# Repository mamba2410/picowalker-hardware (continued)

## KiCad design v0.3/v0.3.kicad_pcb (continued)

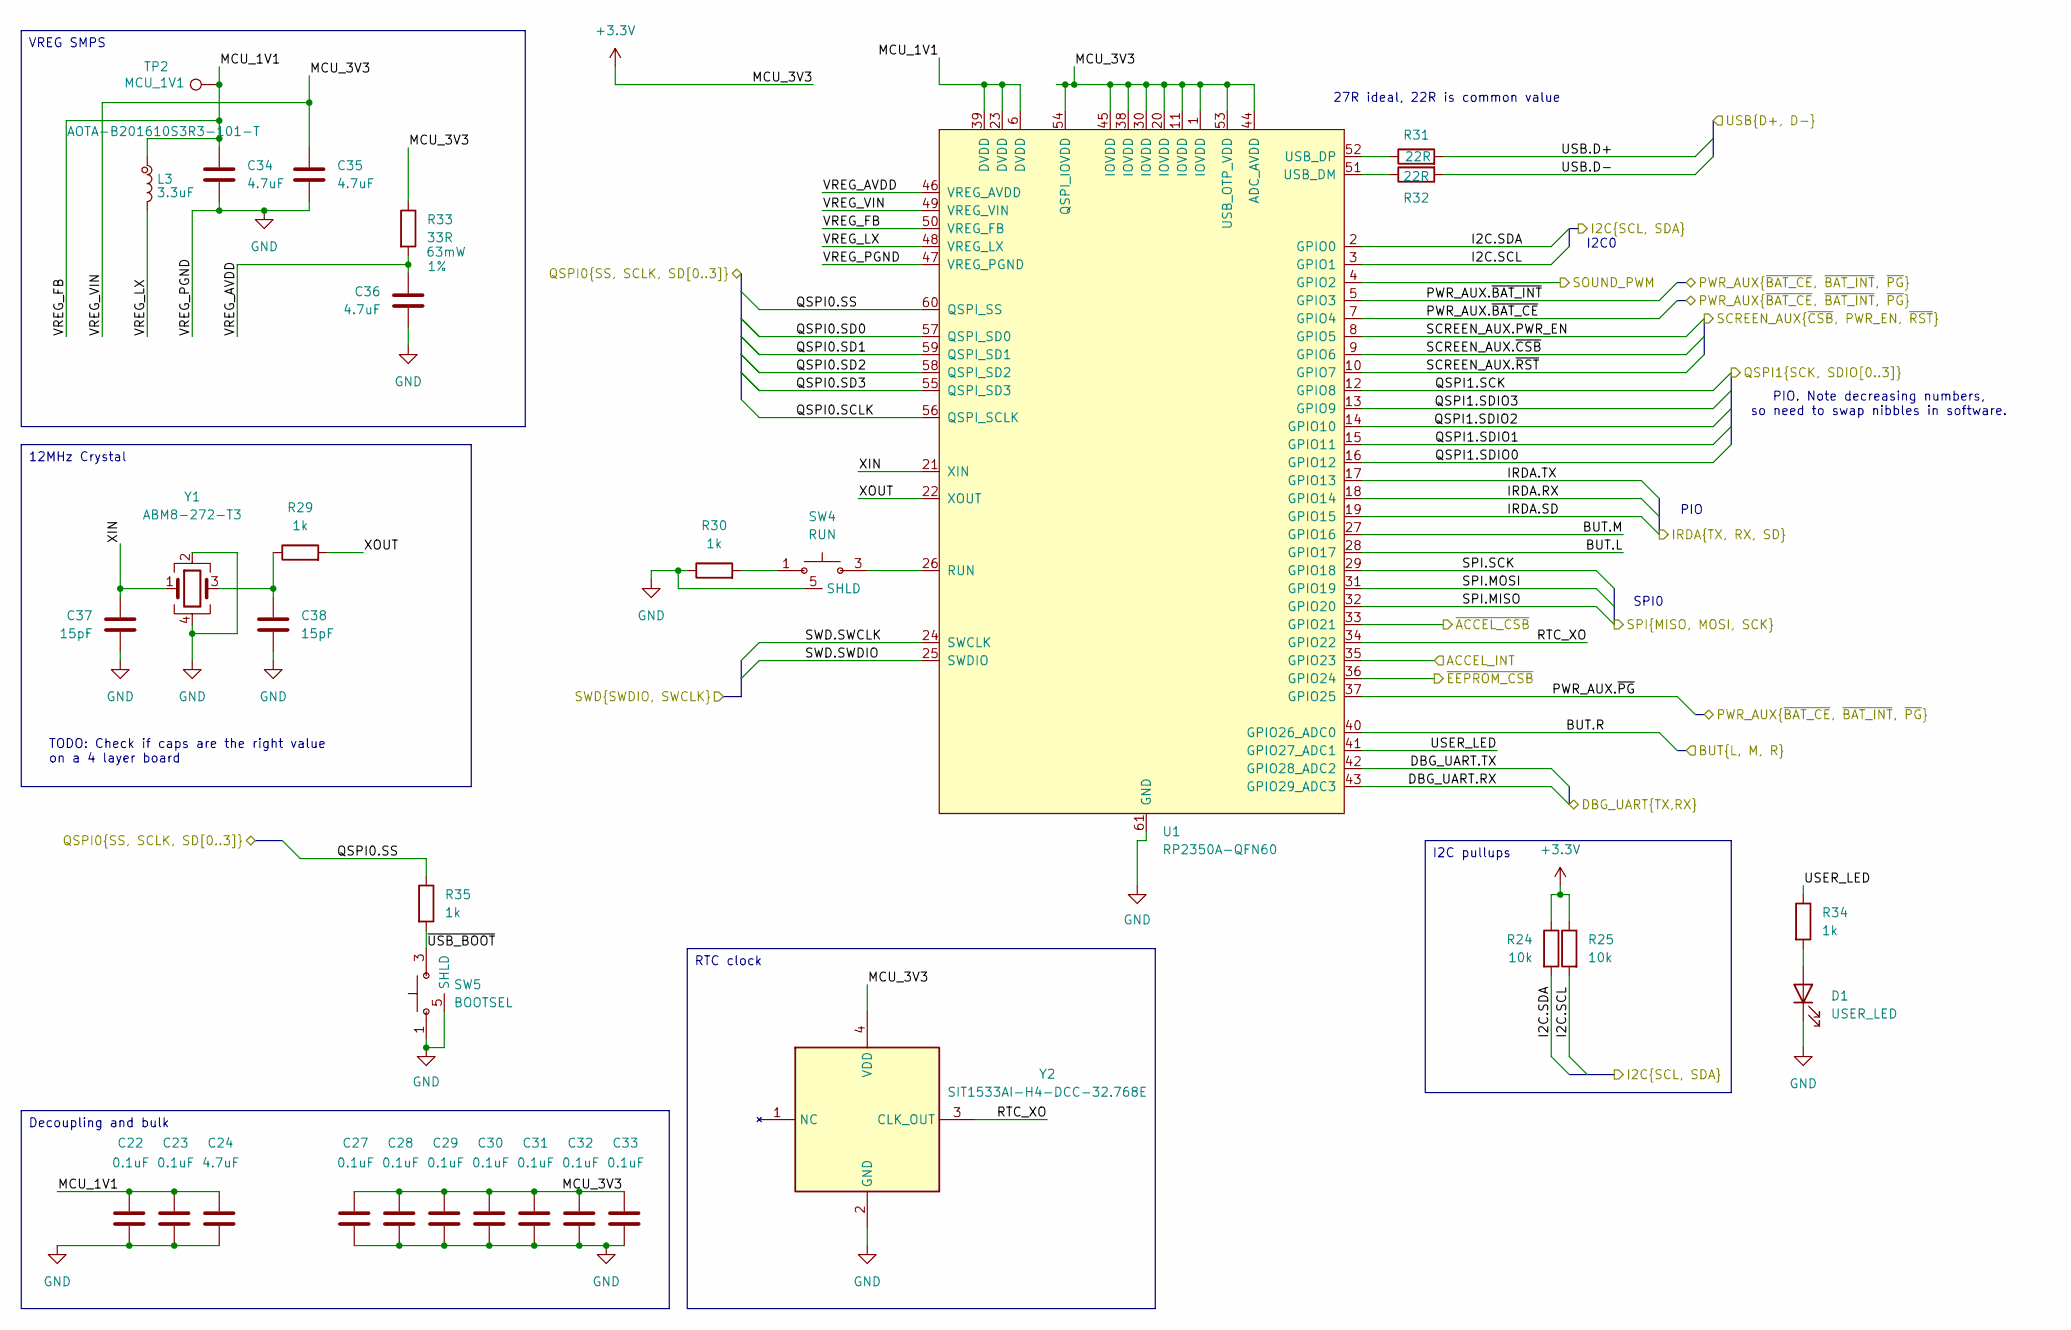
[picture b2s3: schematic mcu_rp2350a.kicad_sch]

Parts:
C22, C23, C27, C28, C29, C30, C31, C32, C33: 0.1uF; C_0402_1005Metric
C24, C34, C35, C36: 4.7uF; C_0402_1005Metric
C37, C38: 15pF; C_0201_0603Metric
D1: USER_LED; LED_0402_1005Metric
L3: 3.3uF; L_0805_2016Metric
R24, R25: 10k; R_0402_1005Metric
R29, R30, R34, R35: 1k; R_0402_1005Metric
R31, R32: 22R; R_0402_1005Metric
R33: 33R; R_0402_1005Metric; Tolerance 1%
SW4: RUN; WS_TASV_435151014824
SW5: BOOTSEL; WS_TASV_435151014824
TP2: MCU_1V1; TestPoint_Pad_1.0x1.0mm
U1: RP2350A-QFN60; RP2350A_QFN-60_EP_7.75x7.75_Pitch0.4mm
Y1: ABM8-272-T3; ABM8272T3
Y2: SIT1533AI-H4-DCC-32.768E; SIT1533AIH4DCC32768E; Mouser Part Number 788-1533AIH4DCC32.76

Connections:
+3.3V: C27.1, C28.1, C29.1, C30.1, C31.1, C32.1, C33.1, C35.1, R24.1, R25.1, R33.1, U1.1 (IOVDD), U1.11 (IOVDD), U1.20 (IOVDD), U1.30 (IOVDD), U1.38 (IOVDD), U1.44 (ADC_AVDD), U1.45 (IOVDD), U1.49 (VREG_VIN), U1.53 (USB_OTP_VDD), U1.54 (QSPI_IOVDD), Y2.4 (VDD); also elsewhere on the board
/accel/ACCEL_INT: U1.35 (GPIO23); also elsewhere on the board
/accel/SPI.MISO: U1.32 (GPIO20); also elsewhere on the board
/accel/SPI.MOSI: U1.31 (GPIO19); also elsewhere on the board
/accel/SPI.SCK: U1.29 (GPIO18); also elsewhere on the board
/accel/~ACCEL_CSB: U1.33 (GPIO21); also elsewhere on the board
/buttons/BUT.L: U1.28 (GPIO17); also elsewhere on the board
/buttons/BUT.M: U1.27 (GPIO16); also elsewhere on the board
/buttons/BUT.R: U1.40 (GPIO26_ADC0); also elsewhere on the board
/connectors/DBG_UART.RX: U1.43 (GPIO29_ADC3); also elsewhere on the board
/connectors/DBG_UART.TX: U1.42 (GPIO28_ADC2); also elsewhere on the board
/connectors/SWD.SWCLK: U1.24 (SWCLK); also elsewhere on the board
/connectors/SWD.SWDIO: U1.25 (SWDIO); also elsewhere on the board
/connectors/USB.D+: R31.2; also elsewhere on the board
/connectors/USB.D-: R32.2; also elsewhere on the board
/eeprom/~EEPROM_CSB: U1.36 (GPIO24); also elsewhere on the board
/flash/QSPI0.SCLK: U1.56 (QSPI_SCLK); also elsewhere on the board
/flash/QSPI0.SD0: U1.57 (QSPI_SD0); also elsewhere on the board
/flash/QSPI0.SD1: U1.59 (QSPI_SD1); also elsewhere on the board
/flash/QSPI0.SD2: U1.58 (QSPI_SD2); also elsewhere on the board
/flash/QSPI0.SD3: U1.55 (QSPI_SD3); also elsewhere on the board
/flash/QSPI0.SS: R35.1, U1.60 (QSPI_SS); also elsewhere on the board
/irda/IRDA.RX: U1.18 (GPIO14); also elsewhere on the board
/irda/IRDA.SD: U1.19 (GPIO15); also elsewhere on the board
/irda/IRDA.TX: U1.17 (GPIO13); also elsewhere on the board
/mcu/I2C.SCL: R25.2, U1.3 (GPIO1); also elsewhere on the board
/mcu/I2C.SDA: R24.2, U1.2 (GPIO0); also elsewhere on the board
/mcu/MCU_1V1: C22.1, C23.1, C24.1, C34.1, L3.1, TP2.1, U1.6 (DVDD), U1.23 (DVDD), U1.39 (DVDD), U1.50 (VREG_FB)
/mcu/PWR_AUX.~BAT_CE: U1.7 (GPIO4); also elsewhere on the board
/mcu/PWR_AUX.~BAT_INT: U1.5 (GPIO3); also elsewhere on the board
/mcu/PWR_AUX.~PG: U1.37 (GPIO25); also elsewhere on the board
/mcu/QSPI1.SCK: U1.12 (GPIO8); also elsewhere on the board
/mcu/QSPI1.SDIO0: U1.16 (GPIO12); also elsewhere on the board
/mcu/QSPI1.SDIO1: U1.15 (GPIO11); also elsewhere on the board
/mcu/QSPI1.SDIO2: U1.14 (GPIO10); also elsewhere on the board
/mcu/QSPI1.SDIO3: U1.13 (GPIO9); also elsewhere on the board
/mcu/RTC_XO: U1.34 (GPIO22), Y2.3 (CLK_OUT)
/mcu/SCREEN_AUX.PWR_EN: U1.8 (GPIO5); also elsewhere on the board
/mcu/SCREEN_AUX.~CSB: U1.9 (GPIO6); also elsewhere on the board
/mcu/SCREEN_AUX.~RST: U1.10 (GPIO7); also elsewhere on the board
/mcu/SOUND_PWM: U1.4 (GPIO2); also elsewhere on the board
/mcu/USER_LED: R34.1, U1.41 (GPIO27_ADC1)
/mcu/VREG_AVDD: C36.1, R33.2, U1.46 (VREG_AVDD)
/mcu/VREG_LX: L3.2, U1.48 (VREG_LX)
/mcu/XIN: C37.1, U1.21 (XIN), Y1.1
/mcu/XOUT: R29.2, U1.22 (XOUT)
/mcu/~USB_BOOT: R35.2, SW5.3, SW5.4
GND: C22.2, C23.2, C24.2, C27.2, C28.2, C29.2, C30.2, C31.2, C32.2, C33.2, C34.2, C35.2, C36.2, C37.2, C38.2, D1.1 (K), R30.1, SW4.5 (SHLD), SW4.6 (SHLD), SW5.1, SW5.2, SW5.5 (SHLD), SW5.6 (SHLD), U1.47 (VREG_PGND), U1.61 (GND), Y1.2, Y1.4, Y2.2 (GND); also elsewhere on the board
unnamed: C38.1, R29.1, Y1.3
unnamed: D1.2 (A), R34.2
unnamed: R30.2, SW4.1, SW4.2
unnamed: SW4.3, SW4.4, U1.26 (RUN)
unnamed: R32.1, U1.51 (USB_DM)
unnamed: R31.1, U1.52 (USB_DP)

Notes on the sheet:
PIO
TODO: Check if caps are the right value on a 4 layer board
PIO. Note decreasing numbers, so need to swap nibbles in software.
SPI0
27R ideal, 22R is common value
I2C0
VREG SMPS
Decoupling and bulk
RTC clock
I2C pullups
12MHz Crystal

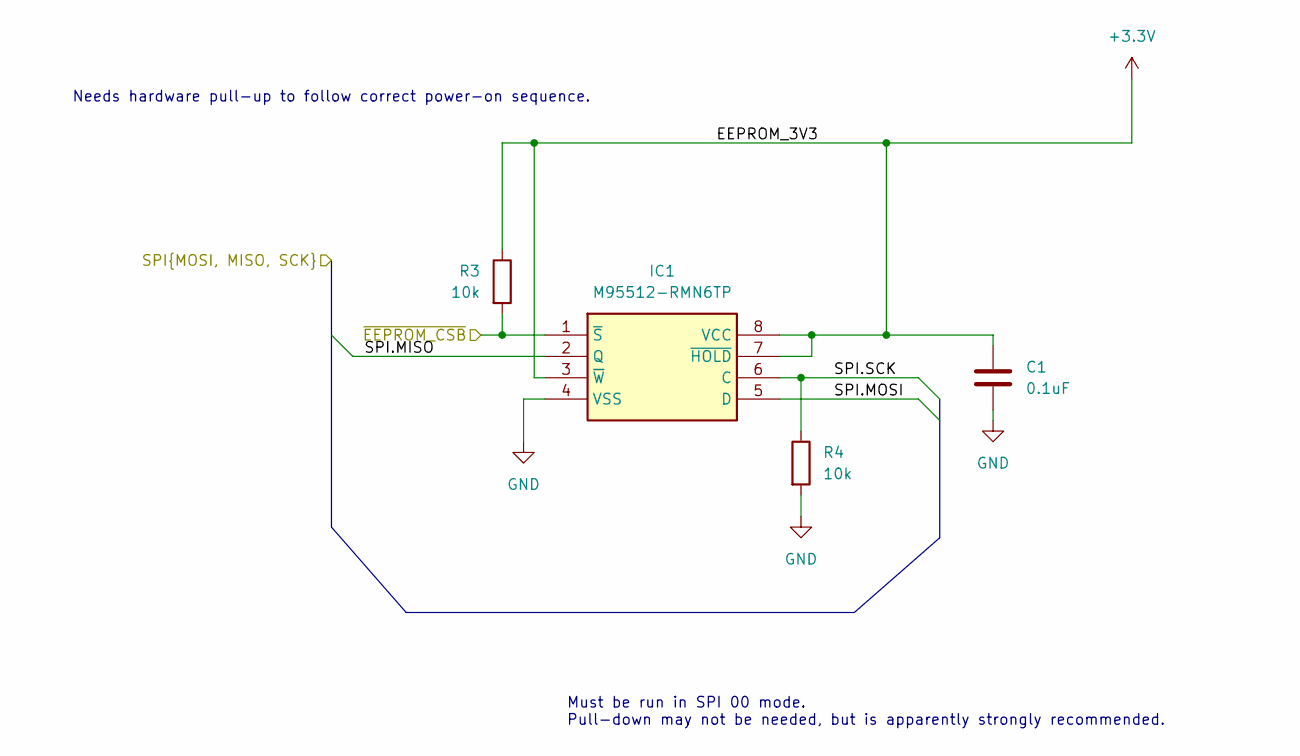
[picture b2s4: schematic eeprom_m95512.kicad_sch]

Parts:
C1: 0.1uF; C_0402_1005Metric
IC1: M95512-RMN6TP; SOIC127P600X175-8N; Mouser Part Number 511-M95512-RMN6TP
R3, R4: 10k; R_0402_1005Metric

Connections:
+3.3V: C1.1, IC1.3 (~W), IC1.7 (~HOLD), IC1.8 (VCC), R3.1; also elsewhere on the board
/accel/SPI.MISO: IC1.2 (Q); also elsewhere on the board
/accel/SPI.MOSI: IC1.5 (D); also elsewhere on the board
/accel/SPI.SCK: IC1.6 (C), R4.1; also elsewhere on the board
/eeprom/~EEPROM_CSB: IC1.1 (~S), R3.2; also elsewhere on the board
GND: C1.2, IC1.4 (VSS), R4.2; also elsewhere on the board

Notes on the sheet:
Needs hardware pull-up to follow correct power-on sequence.
Must be run in SPI 00 mode. Pull-down may not be needed, but is apparently strongly recommended.

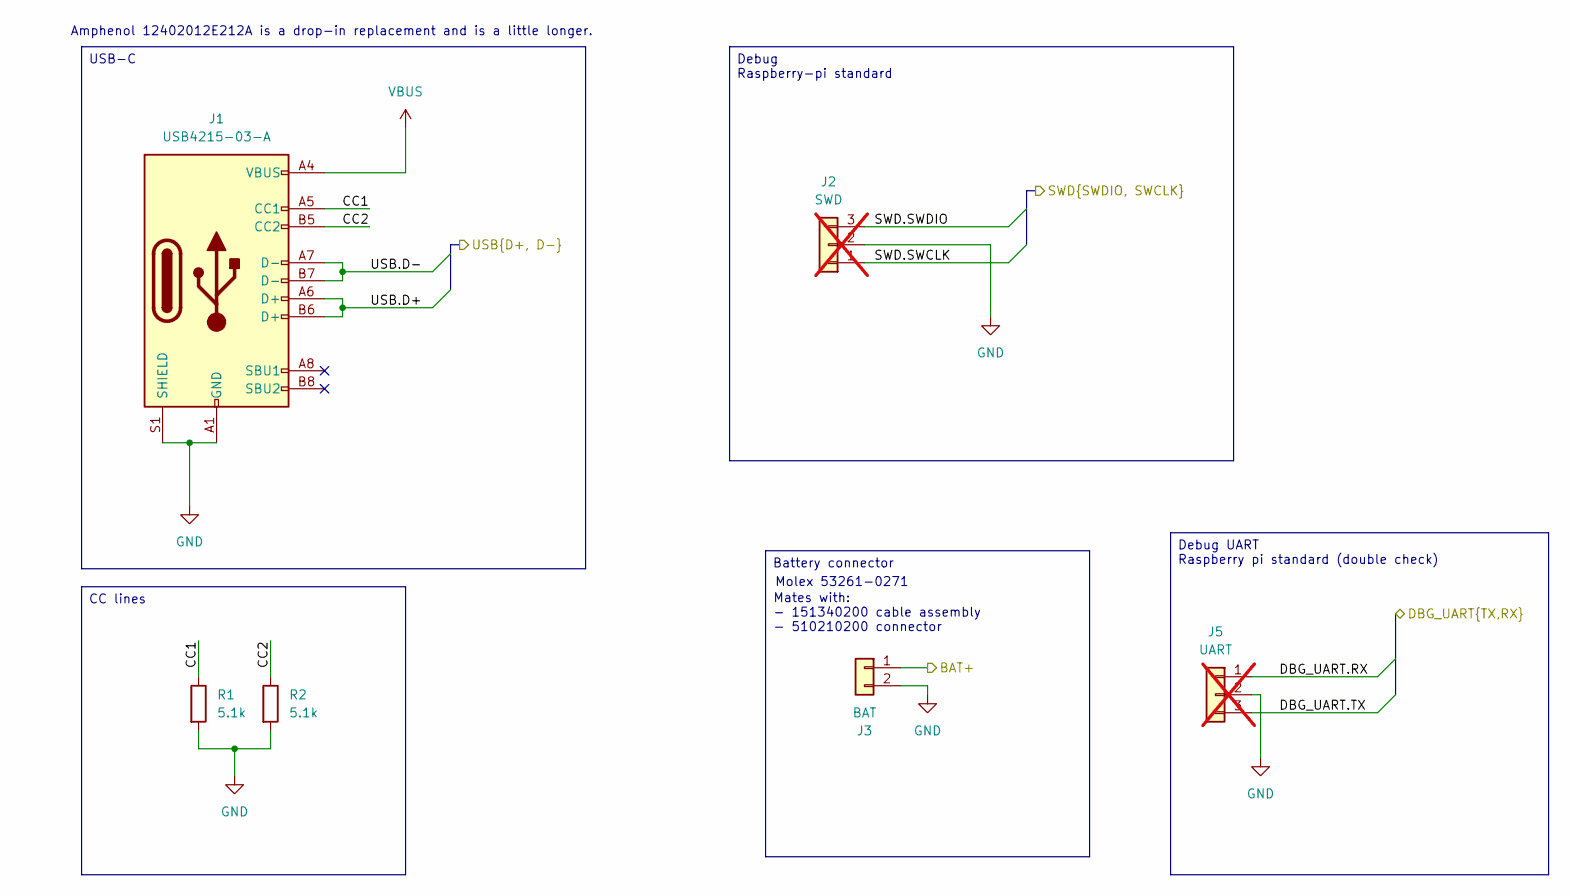
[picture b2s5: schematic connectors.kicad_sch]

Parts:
J1: USB4215-03-A; GCT_USB4215_03_A
J2: SWD; JST_SH_SM03B-SRSS-TB_1x03-1MP_P1.00mm_Horizontal; not fitted
J3: BAT; Molex_PicoBlade_53261-0271_1x02-1MP_P1.25mm_Horizontal
J5: UART; JST_SH_SM03B-SRSS-TB_1x03-1MP_P1.00mm_Horizontal; not fitted
R1, R2: 5.1k; R_0402_1005Metric

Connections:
/connectors/BAT+: J3.1; also elsewhere on the board
/connectors/CC1: J1.A5 (CC1), R1.1
/connectors/CC2: J1.B5 (CC2), R2.1
/connectors/DBG_UART.RX: J5.1; also elsewhere on the board
/connectors/DBG_UART.TX: J5.3; also elsewhere on the board
/connectors/SWD.SWCLK: J2.1; also elsewhere on the board
/connectors/SWD.SWDIO: J2.3; also elsewhere on the board
/connectors/USB.D+: J1.A6 (D+), J1.B6 (D+); also elsewhere on the board
/connectors/USB.D-: J1.A7 (D-), J1.B7 (D-); also elsewhere on the board
GND: J1.A1 (GND), J1.A12 (GND), J1.B1 (GND), J1.B12 (GND), J1.S1 (SHIELD), J2.2, J3.2, J5.2, R1.2, R2.2; also elsewhere on the board
VBUS: J1.A4 (VBUS), J1.A9 (VBUS), J1.B4 (VBUS), J1.B9 (VBUS); also elsewhere on the board

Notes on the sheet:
Amphenol 12402012E212A is a drop-in replacement and is a little longer.
Mates with: - 151340200 cable assembly - 510210200 connector
Molex 53261-0271
Debug UART Raspberry pi standard (double check)
USB-C
Debug Raspberry-pi standard
CC lines
Battery connector

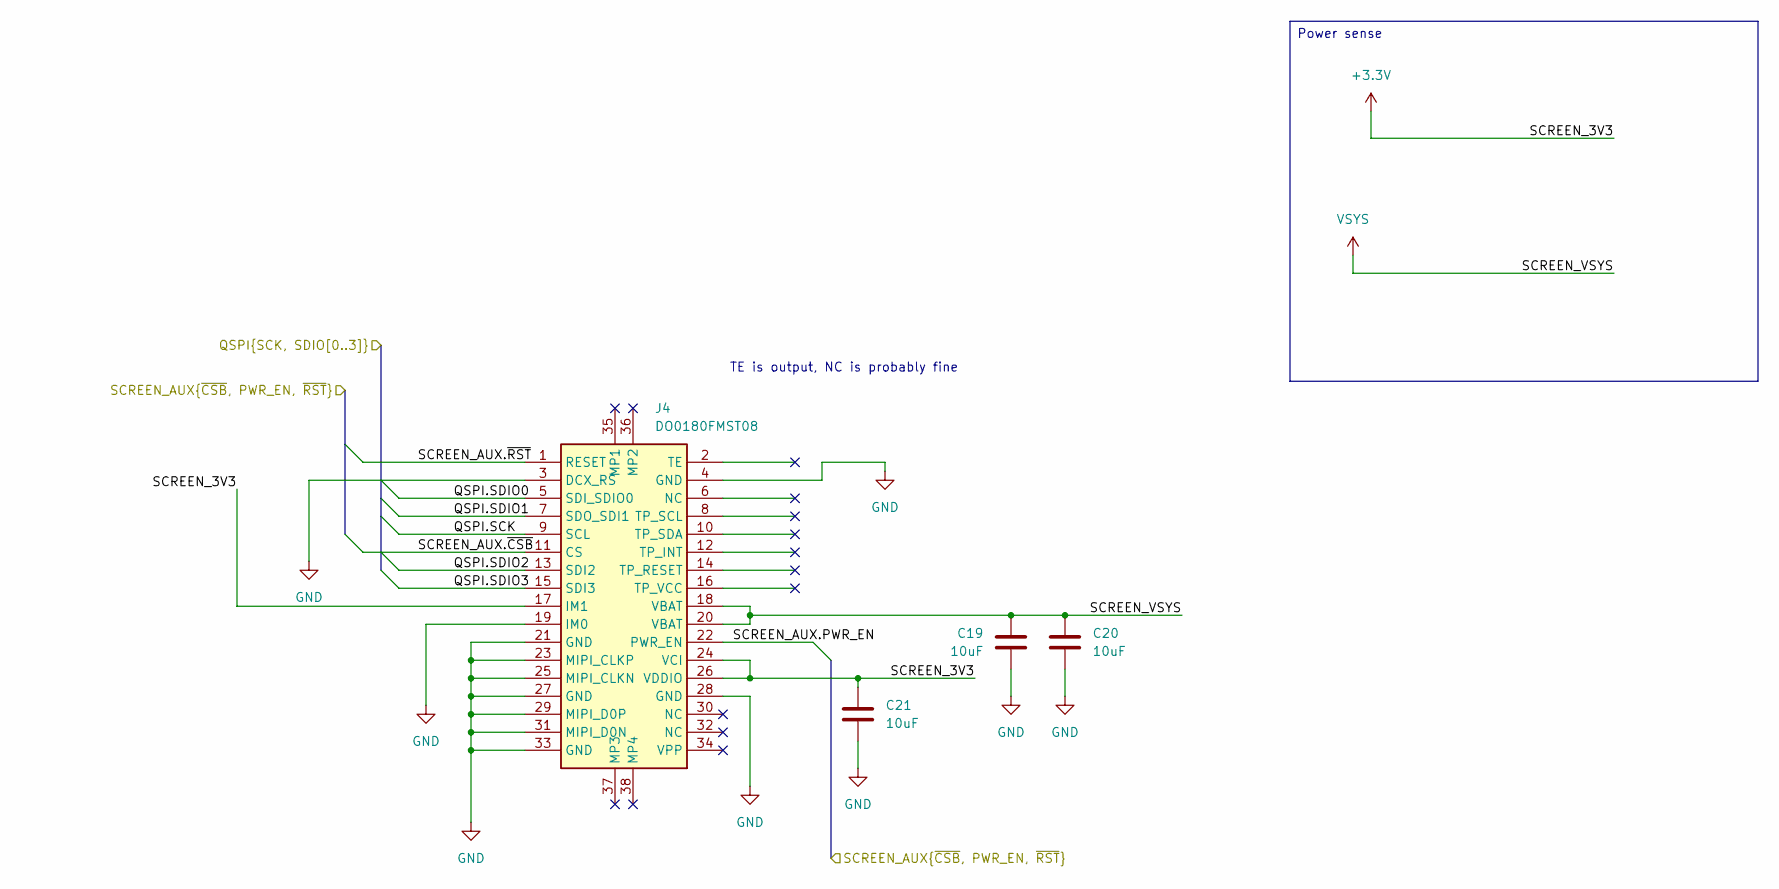
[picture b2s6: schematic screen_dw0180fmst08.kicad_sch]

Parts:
C19, C20, C21: 10uF; C_0603_1608Metric
J4: DO0180FMST08; AXE534127; Mouser Part Number 679-AXE534127

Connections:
+3.3V: C21.1, J4.17 (IM1), J4.24 (VCI), J4.26 (VDDIO); also elsewhere on the board
/mcu/QSPI1.SCK: J4.9 (SCL); also elsewhere on the board
/mcu/QSPI1.SDIO0: J4.5 (SDI_SDIO0); also elsewhere on the board
/mcu/QSPI1.SDIO1: J4.7 (SDO_SDI1); also elsewhere on the board
/mcu/QSPI1.SDIO2: J4.13 (SDI2); also elsewhere on the board
/mcu/QSPI1.SDIO3: J4.15 (SDI3); also elsewhere on the board
/mcu/SCREEN_AUX.PWR_EN: J4.22 (PWR_EN); also elsewhere on the board
/mcu/SCREEN_AUX.~CSB: J4.11 (CS); also elsewhere on the board
/mcu/SCREEN_AUX.~RST: J4.1 (RESET); also elsewhere on the board
GND: C19.1, C20.2, C21.2, J4.3 (DCX_RS), J4.4 (GND), J4.19 (IM0), J4.21 (GND), J4.23 (MIPI_CLKP), J4.25 (MIPI_CLKN), J4.27 (GND), J4.28 (GND), J4.29 (MIPI_D0P), J4.31 (MIPI_D0N), J4.33 (GND); also elsewhere on the board
VSYS: C19.2, C20.1, J4.18 (VBAT), J4.20 (VBAT); also elsewhere on the board

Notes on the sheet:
TE is output, NC is probably fine
Power sense

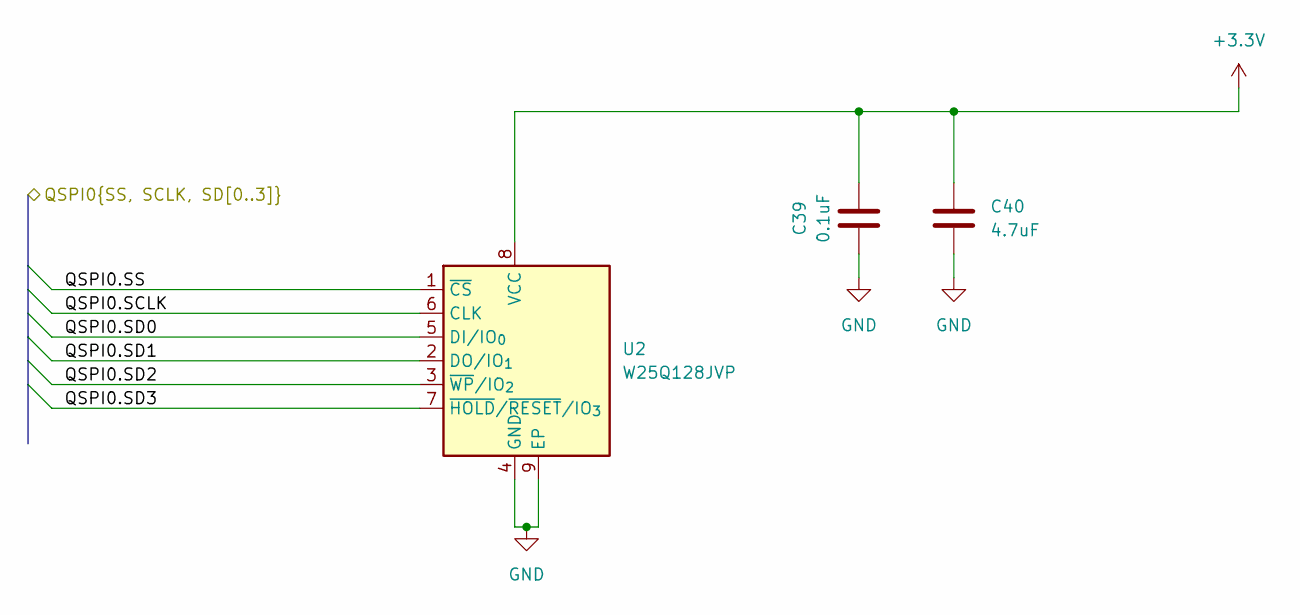
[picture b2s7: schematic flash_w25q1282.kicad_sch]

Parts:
C39: 0.1uF; C_0402_1005Metric
C40: 4.7uF; C_0402_1005Metric
U2: W25Q128JVP; WSON-8-1EP_6x5mm_P1.27mm_EP3.4x4.3mm

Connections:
+3.3V: C39.1, C40.1, U2.8 (VCC); also elsewhere on the board
/flash/QSPI0.SCLK: U2.6 (CLK); also elsewhere on the board
/flash/QSPI0.SD0: U2.5 (DI/IO_{0}); also elsewhere on the board
/flash/QSPI0.SD1: U2.2 (DO/IO_{1}); also elsewhere on the board
/flash/QSPI0.SD2: U2.3 (~WP/IO_{2}); also elsewhere on the board
/flash/QSPI0.SD3: U2.7 (~HOLD/~RESET/IO_{3}); also elsewhere on the board
/flash/QSPI0.SS: U2.1 (~CS); also elsewhere on the board
GND: C39.2, C40.2, U2.4 (GND), U2.9 (EP); also elsewhere on the board

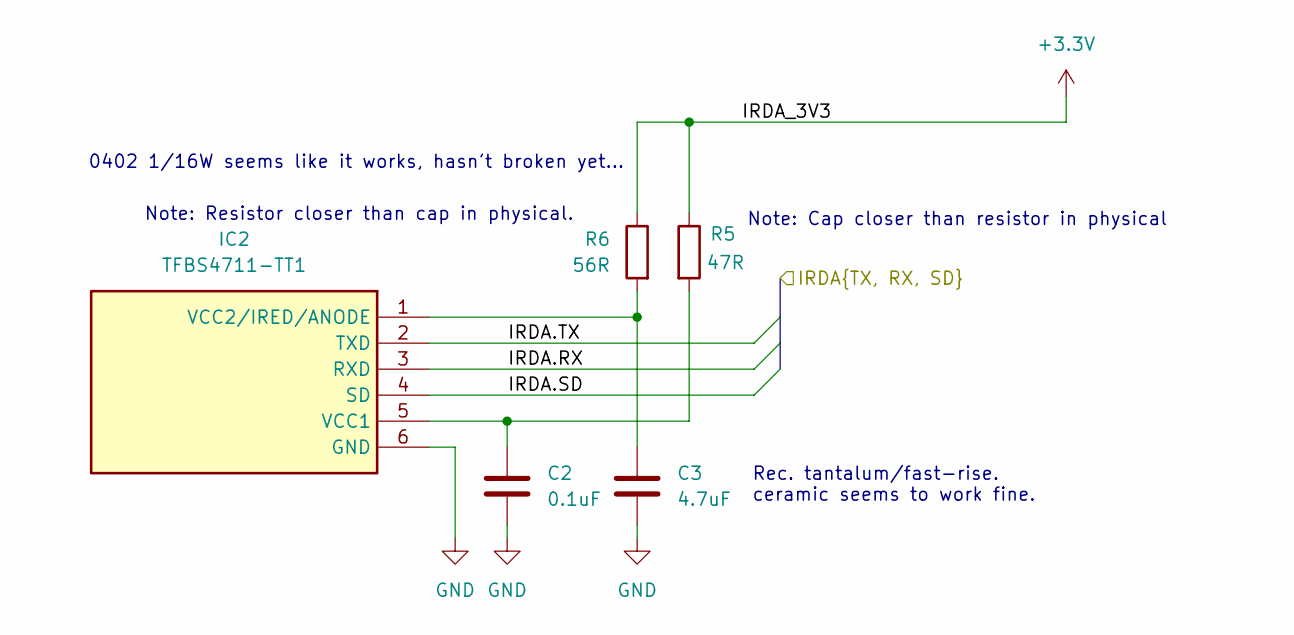
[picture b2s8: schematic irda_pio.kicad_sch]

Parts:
C2: 0.1uF; C_0402_1005Metric
C3: 4.7uF; C_0402_1005Metric
IC2: TFBS4711-TT1; TFBS4711-TR; Mouser Part Number 782-TFBS4711-TT1
R5: 47R; R_0402_1005Metric
R6: 56R; R_0402_1005Metric

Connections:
+3.3V: R5.1, R6.1; also elsewhere on the board
/irda/IRDA.RX: IC2.3 (RXD); also elsewhere on the board
/irda/IRDA.SD: IC2.4 (SD); also elsewhere on the board
/irda/IRDA.TX: IC2.2 (TXD); also elsewhere on the board
GND: C2.2, C3.2, IC2.6 (GND); also elsewhere on the board
unnamed: C2.1, IC2.5 (VCC1), R5.2
unnamed: C3.1, IC2.1 (VCC2/IRED/ANODE), R6.2

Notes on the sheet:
Rec. tantalum/fast-rise. ceramic seems to work fine.
0402 1/16W seems like it works, hasn't broken yet...
Note: Cap closer than resistor in physical
Note: Resistor closer than cap in physical.

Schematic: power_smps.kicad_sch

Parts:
C9: 47nF; C_0603_1608Metric
C10, C11, C12, C14, C16: 10uF; C_0603_1608Metric
C13: 0.1uF; C_0402_1005Metric
C15: 4.7uF; C_0603_1608Metric
C17, C18: 47uF; C_0805_2012Metric; Tolerance 20%
D2: ~{STAT}; LED_0402_1005Metric
IC3: BQ25628ERYKR; Mouser Part Number 595-BQ25628ERYKR
IC4: RT6150B-33GQW; SON50P250X250X80-11N-D
L1: 1uH; L_0603_1608Metric
L2: 2.2uH; L_0805_2012Metric
R13: 5.3k; R_0402_1005Metric
R14: 30k; R_0603_1608Metric
R15: 5k; R_0402_1005Metric
R17: 1k; R_0402_1005Metric
R18, R19: 100k; R_0603_1608Metric
R20: 10k; R_0402_1005Metric
TH1: 10k; R_0402_1005Metric_Sunken
TP1: ~{QON}; TestPoint_Pad_1.0x1.0mm

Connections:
+3.3V: C17.1, IC4.1 (VOUT), IC4.10 (FB), R17.1, R20.1; also elsewhere on the board
/connectors/BAT+: C16.1, IC3.8 (BAT); also elsewhere on the board
/mcu/I2C.SCL: IC3.13 (SCL); also elsewhere on the board
/mcu/I2C.SDA: IC3.12 (SDA); also elsewhere on the board
/mcu/PWR_AUX.~BAT_CE: IC3.14 (~CE_1), IC3.22 (~CE_2); also elsewhere on the board
/mcu/PWR_AUX.~BAT_INT: IC3.11 (~INT); also elsewhere on the board
/mcu/PWR_AUX.~PG: IC3.3 (~PG), R20.2; also elsewhere on the board
/power/3V3_EN: IC4.6 (EN), R19.2
/power/BTST: C9.2, IC3.1 (BTST_1), IC3.19 (BTST_2)
/power/ILIM: IC3.4 (ILIM), R15.1
/power/PMID: C13.1, C14.1, IC3.17 (PMID)
/power/PS: IC4.7 (PS), R18.1
/power/REGN: C15.1, IC3.2 (REGN)
/power/SW: C9.1, IC3.16 (SW), L1.1
/power/TS: IC3.6 (TS), R13.2, R14.1, TH1.1
/power/TS_BIAS: IC3.5 (TS_BIAS_1), IC3.20 (TS_BIAS_2), R13.1
/power/~QON: IC3.7 (~QON), TP1.1
/power/~STAT: D2.1 (K), IC3.10 (STAT_1), IC3.21 (STAT_2)
GND: C10.2, C11.2, C12.2, C13.2, C14.2, C15.2, C16.2, C17.2, C18.2, IC3.15 (GND), IC4.3 (GND), IC4.9 (GND), IC4.11 (GND_PAD), R14.2, R15.2, R18.2, TH1.2; also elsewhere on the board
unnamed: D2.2 (A), R17.2
unnamed: IC4.4 (LX1), L2.1
unnamed: IC4.2 (LX2), L2.2
VBUS: C12.1, IC3.18 (VBUS); also elsewhere on the board
VSYS: C10.1, C11.1, C18.1, IC3.9 (SYS), IC4.5 (VIN), IC4.8 (VINA), L1.2, R19.1; also elsewhere on the board

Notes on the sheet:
Can be software disabled
I_ILIM = K_ILIM/R_ILIM K_ILIM = 2500 +/-250
Datasheet: 30.1k
Ceramic! As close to pins as possible
RT0402DRE075K3L
Decoupling and bulk, place as close to PMID/GND pins as possible
Datasheet: 5.32k
ERA-3AED303V
3.3V switching regulator Basically taken from pico 2 datasheet/schematic
Battery decouple
Thermistor
PMID pin
PMIC battery charger with power path
REGN pin
Indicator LEDs
ILIM pin
Output conditioning

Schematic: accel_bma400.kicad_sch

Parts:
AC1: BMA400; BOSCH_LGA-12; Mouser Part Number 262-BMA400
C4, C5: 0.1uF; C_0402_1005Metric

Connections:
+3.3V: AC1.3 (VDDIO), AC1.7 (VDD), C4.1, C5.1; also elsewhere on the board
/accel/ACCEL_INT: AC1.5 (INT1); also elsewhere on the board
/accel/SPI.MISO: AC1.1 (SDO); also elsewhere on the board
/accel/SPI.MOSI: AC1.2 (SDX); also elsewhere on the board
/accel/SPI.SCK: AC1.12 (SCX); also elsewhere on the board
/accel/~ACCEL_CSB: AC1.10 (CSB); also elsewhere on the board
GND: AC1.8 (GNDIO), AC1.9 (GND), C4.2, C5.2; also elsewhere on the board

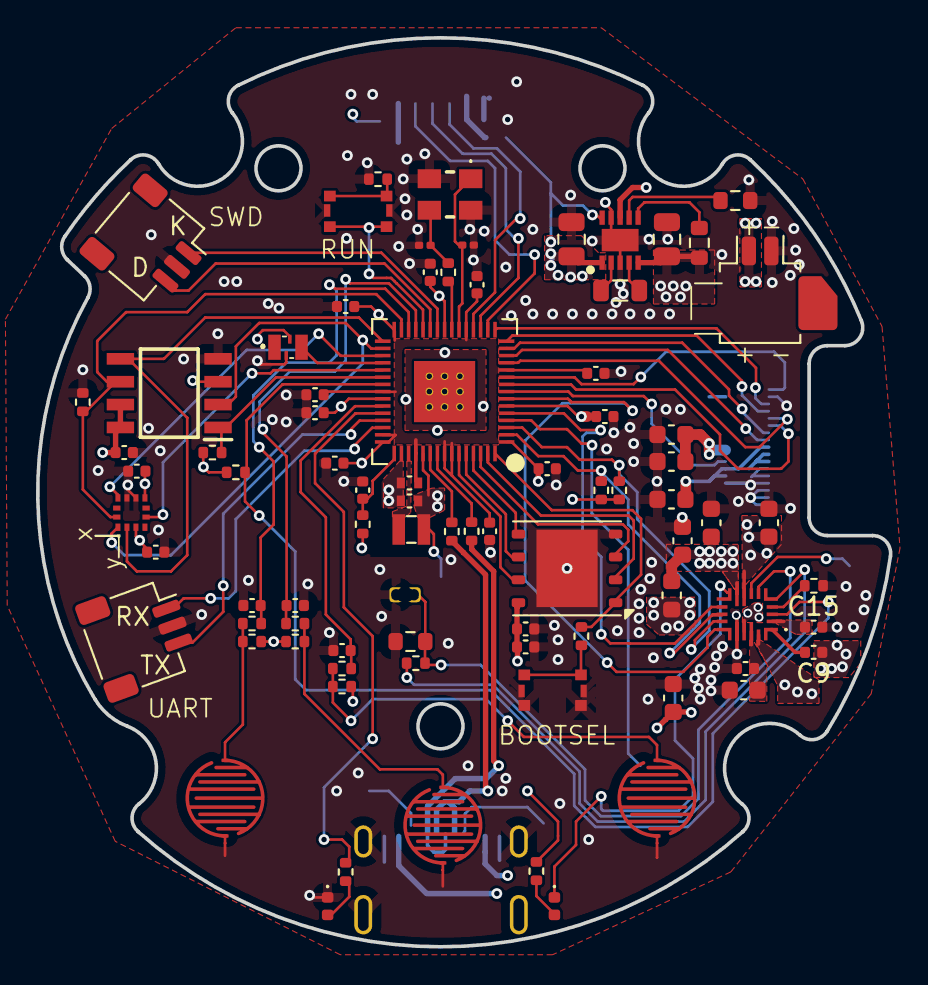
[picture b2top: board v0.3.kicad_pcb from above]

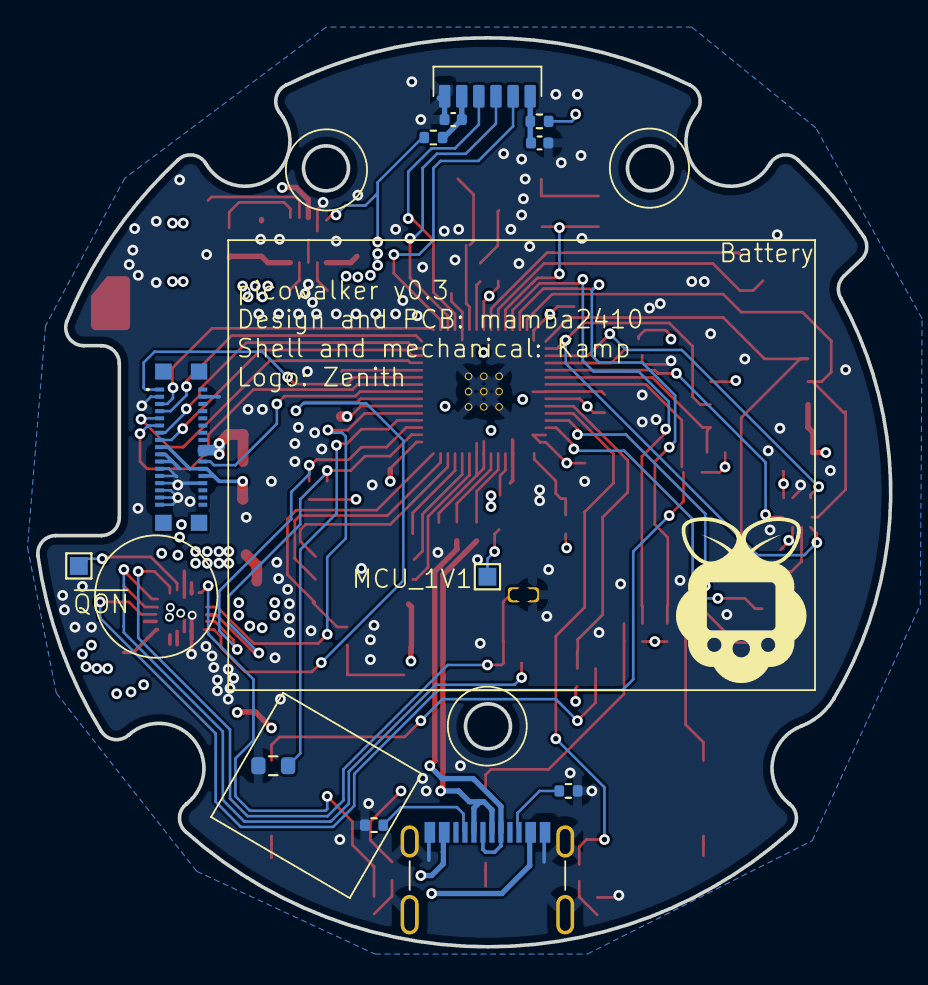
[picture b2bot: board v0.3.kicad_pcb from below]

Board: 4 copper layers, 47.4 x 50.5 mm, 94 parts (13 on the bottom side), 78 nets.

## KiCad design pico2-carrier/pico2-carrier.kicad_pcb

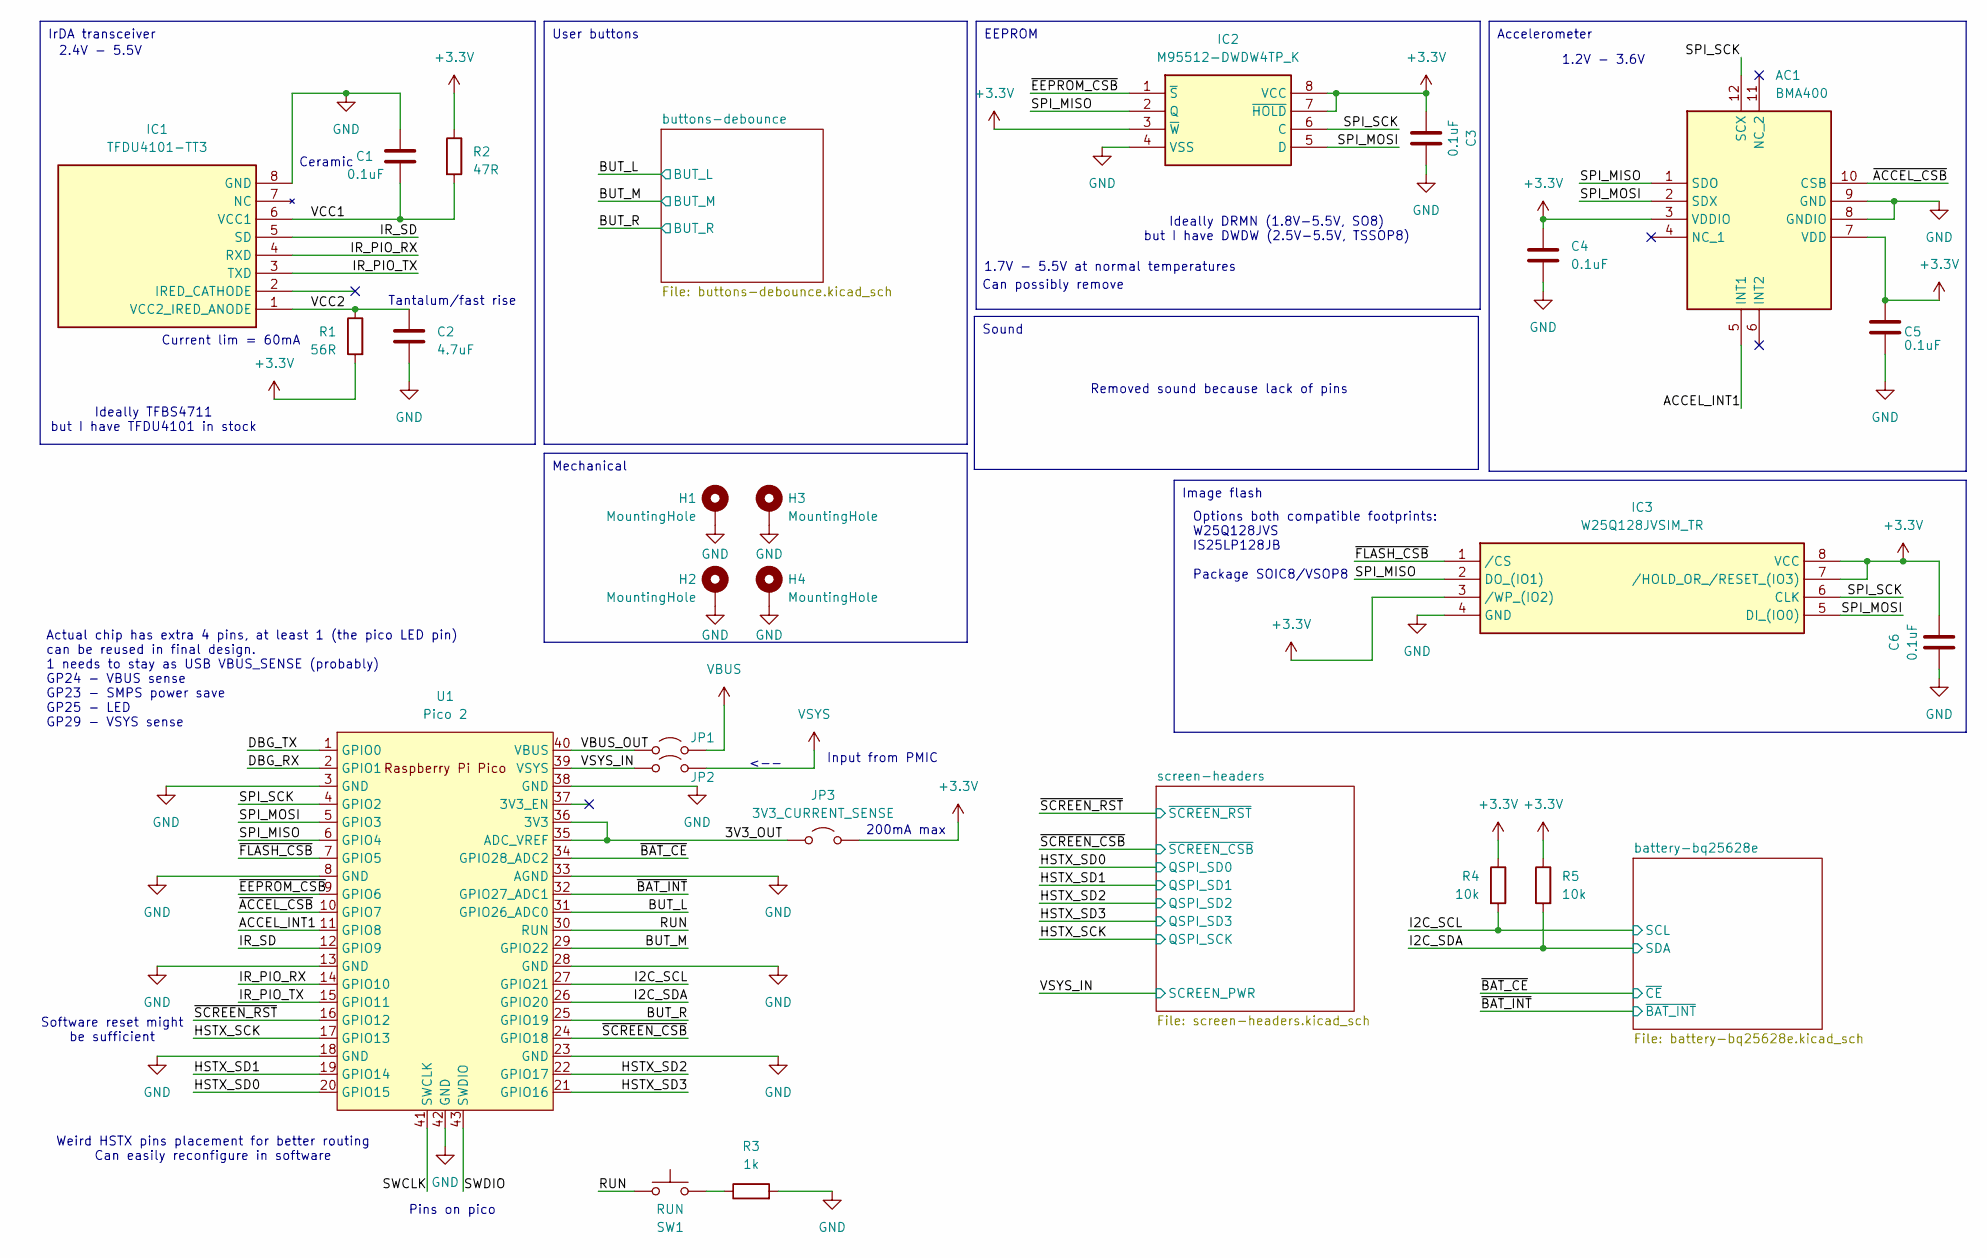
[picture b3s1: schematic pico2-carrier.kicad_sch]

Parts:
AC1: BMA400; BOSCH_LGA-12; Mouser Part Number 262-BMA400
C1, C3, C4, C5, C6: 0.1uF; C_0402_1005Metric
C2: 4.7uF; C_0603_1608Metric
H1, H2, H3, H4: MountingHole; MountingHole_2.2mm_M2_DIN965_Pad_TopBottom
IC1: TFDU4101-TT3; TFDU4101-TR3-Side; Mouser Part Number 782-TFDU4101-TT3
IC2: M95512-DWDW4TP_K; SOP65P640X120-8N; Mouser Part Number 511-M95512-DWDW4TP/K
IC3: W25Q128JVSIM_TR; SOIC127P790X216-8N; Mouser Part Number 454-W25Q128JVSIMTR
JP1: VBUS_SENSE; PinHeader_1x02_P2.54mm_Vertical
JP2: VSYS_SENSE; PinHeader_1x02_P2.54mm_Vertical
JP3: 3V3_CURRENT_SENSE; PinHeader_1x02_P2.54mm_Vertical
R1: 56R; R_0402_1005Metric
R2: 47R; R_0402_1005Metric
R3: 1k; R_0402_1005Metric
R4, R5: 10k; R_0402_1005Metric
SW1: RUN; SW_SPST_Omron_B3FS-101xP
U1: Pico 2; RPi_Pico_SMD_TH

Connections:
+3.3V: AC1.3 (VDDIO), AC1.7 (VDD), C3.1, C4.1, C5.2, C6.1, IC2.3 (~W), IC2.7 (~HOLD), IC2.8 (VCC), IC3.3 (/WP_(IO2)), IC3.7 (/HOLD_OR_/RESET_(IO3)), IC3.8 (VCC), JP3.2 (B), R1.2, R2.1, R4.1, R5.1; also elsewhere on the board
/3V3_OUT: JP3.1 (A), U1.35 (ADC_VREF), U1.36 (3V3)
/ACCEL_INT1: AC1.5 (INT1), U1.11 (GPIO8)
/BUT_L: U1.31 (GPIO26_ADC0); also elsewhere on the board
/BUT_M: U1.29 (GPIO22); also elsewhere on the board
/BUT_R: U1.25 (GPIO19); also elsewhere on the board
/DBG_RX: U1.2 (GPIO1)
/DBG_TX: U1.1 (GPIO0)
/HSTX_SCK: U1.17 (GPIO13); also elsewhere on the board
/HSTX_SD0: U1.20 (GPIO15); also elsewhere on the board
/HSTX_SD1: U1.19 (GPIO14); also elsewhere on the board
/HSTX_SD2: U1.22 (GPIO17); also elsewhere on the board
/HSTX_SD3: U1.21 (GPIO16); also elsewhere on the board
/I2C_SCL: R4.2, U1.27 (GPIO21); also elsewhere on the board
/I2C_SDA: R5.2, U1.26 (GPIO20); also elsewhere on the board
/IR_PIO_RX: IC1.4 (RXD), U1.14 (GPIO10)
/IR_PIO_TX: IC1.3 (TXD), U1.15 (GPIO11)
/IR_SD: IC1.5 (SD), U1.12 (GPIO9)
/RUN: SW1.2, U1.30 (RUN)
/SPI_MISO: AC1.1 (SDO), IC2.2 (Q), IC3.2 (DO_(IO1)), U1.6 (GPIO4)
/SPI_MOSI: AC1.2 (SDX), IC2.5 (D), IC3.5 (DI_(IO0)), U1.5 (GPIO3)
/SPI_SCK: AC1.12 (SCX), IC2.6 (C), IC3.6 (CLK), U1.4 (GPIO2)
/SWCLK: U1.41 (SWCLK)
/SWDIO: U1.43 (SWDIO)
/VBUS_OUT: JP1.1 (A), U1.40 (VBUS)
/VCC1: C1.2, IC1.6 (VCC1), R2.2
/VCC2: C2.1, IC1.1 (VCC2_IRED_ANODE), R1.1
/VSYS_IN: JP2.1 (A), U1.39 (VSYS); also elsewhere on the board
/~ACCEL_CSB: AC1.10 (CSB), U1.10 (GPIO7)
/~BAT_CE: U1.34 (GPIO28_ADC2); also elsewhere on the board
/~BAT_INT: U1.32 (GPIO27_ADC1); also elsewhere on the board
/~EEPROM_CSB: IC2.1 (~S), U1.9 (GPIO6)
/~FLASH_CSB: IC3.1 (/CS), U1.7 (GPIO5)
/~SCREEN_CSB: U1.24 (GPIO18); also elsewhere on the board
/~SCREEN_RST: U1.16 (GPIO12); also elsewhere on the board
GND: AC1.8 (GNDIO), AC1.9 (GND), C1.1, C2.2, C3.2, C4.2, C5.1, C6.2, H1.1, H2.1, H3.1, H4.1, IC1.8 (GND), IC2.4 (VSS), IC3.4 (GND), R3.2, U1.3 (GND), U1.8 (GND), U1.13 (GND), U1.18 (GND), U1.23 (GND), U1.28 (GND), U1.33 (AGND), U1.38 (GND), U1.42 (GND); also elsewhere on the board
unnamed: R3.1, SW1.1
VBUS: JP1.2 (B); also elsewhere on the board
VSYS: JP2.2 (B); also elsewhere on the board

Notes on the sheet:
User buttons
Accelerometer
Sound
Image flash
Mechanical
IrDA transceiver
EEPROM
Can possibly remove
2.4V - 5.5V
Input from PMIC
200mA max
Software reset might be sufficient
Current lim = 60mA
1.7V - 5.5V at normal temperatures
Actual chip has extra 4 pins, at least 1 (the pico LED pin) can be reused in final design. 1 needs to stay as USB VBUS_SENSE (probably) GP24 - VBUS sense GP23 - SMPS power save GP25 - LED GP29 - VSYS sense
Pins on pico
Ideally DRMN (1.8V-5.5V, SO8) but I have DWDW (2.5V-5.5V, TSSOP8)
Tantalum/fast rise
Ideally TFBS4711 but I have TFDU4101 in stock
Options both compatible footprints: W25Q128JVS IS25LP128JB Package SOIC8/VSOP8
1.2V - 3.6V
Weird HSTX pins placement for better routing Can easily reconfigure in software
Ceramic
<--
Removed sound because lack of pins
